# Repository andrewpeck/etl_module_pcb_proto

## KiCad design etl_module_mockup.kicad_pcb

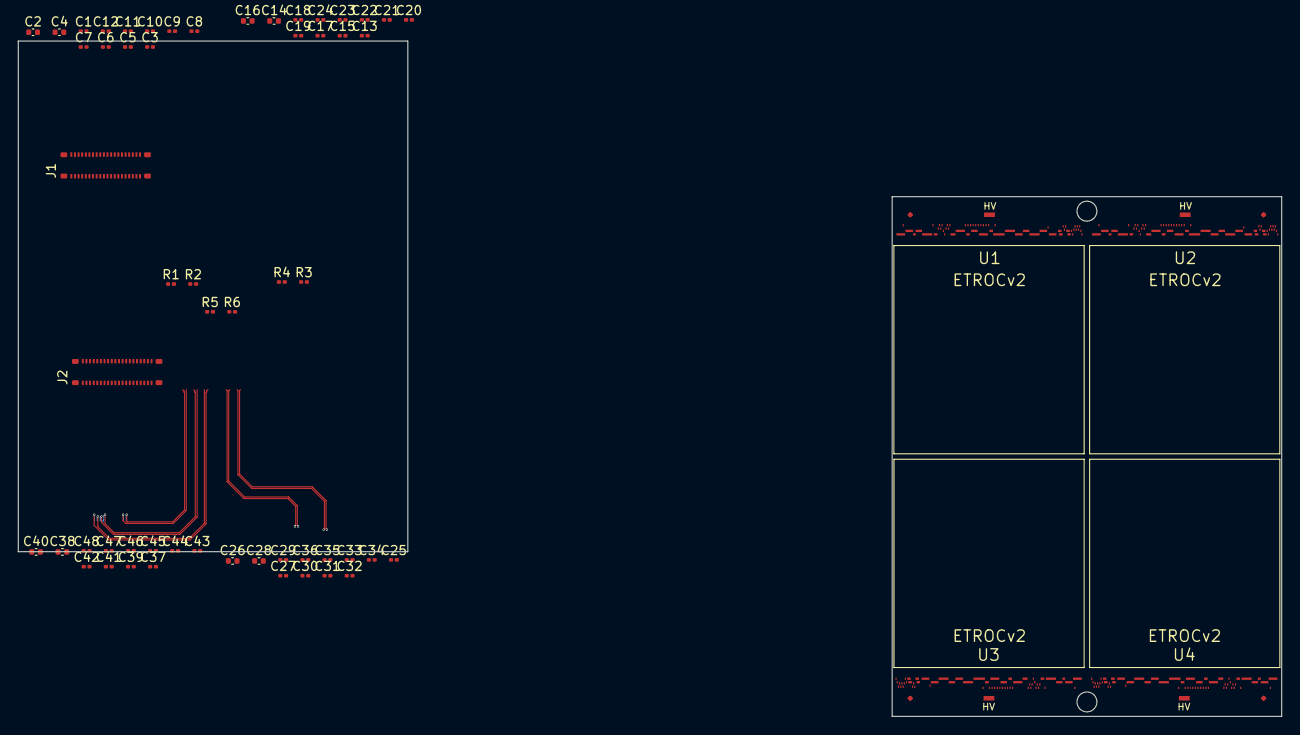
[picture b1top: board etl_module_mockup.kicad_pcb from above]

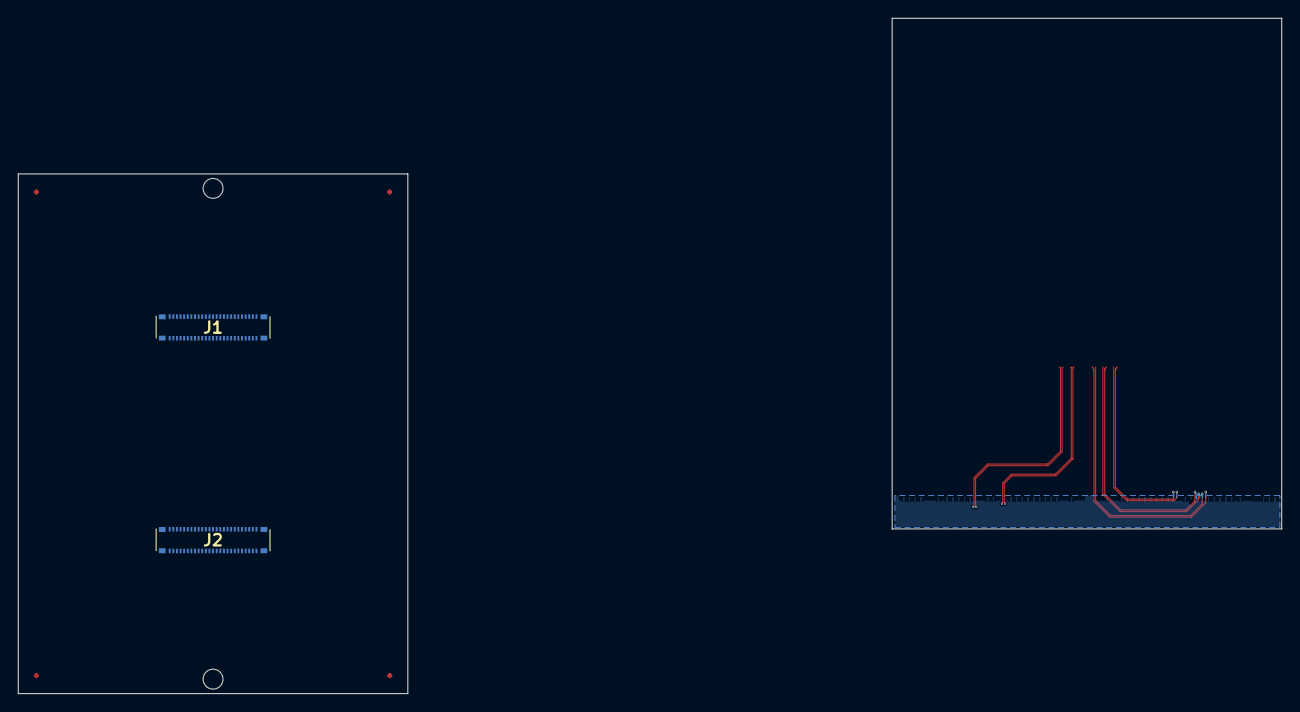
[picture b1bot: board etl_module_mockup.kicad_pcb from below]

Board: 2 copper layers, 62 parts (2 on the bottom side), 34 nets.

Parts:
C1, C3, C5, C6, C7, C8, C9, C10, C11, C12, C13, C15, C17, C18, C19, C20, C21, C22, C23, C24, C25, C27, C29, C30, C31, C32, C33, C34, C35, C36, C37, C39, C41, C42, C43, C44, C45, C46, C47, C48: 0.1uF; C_0201_0603Metric
C2, C4, C14, C16, C26, C28, C38, C40: 1uF; C_0402_1005Metric
J1, J2: WP7B-S040VA1
J1#2, J2#2: WP7B-S050VA1-R8000; WP7BS050VA1R8000
R1: 0R; R_0201_0603Metric
R2, R3, R4: 10k; R_0201_0603Metric
R5, R6: 1.2k 0.5%; R_0201_0603Metric
U1, U2, U3, U4: ETROCv2; PCB_ETROC2_test

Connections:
/1V0A: J1.20, R1.2
/1V2A: C38.1, C39.1, C40.1, C41.1, C42.1, C43.1, C44.1, C45.1, C46.1, C47.1, C48.1, J1.1, J1.2, J1.3, J1.4, J1.5, R2.1, R3.1, R4.1, R6.1, U4.1, U4.3, U4.5, U4.7, U4.13, U4.16, U4.18, U4.20, U4.22, U4.24, U4.30, U4.32, U4.38, U4.40, U4.42
/1V2B: C14.1, C15.1, C16.1, C17.1, C18.1, C19.1, C20.1, C21.1, C22.1, C23.1, C24.1, J1.6, J1.7, J1.8, J1.9, J1.10, U2.1, U2.3, U2.5, U2.7, U2.9, U2.13, U2.16, U2.18, U2.20, U2.22, U2.24, U2.30, U2.32, U2.38, U2.40, U2.42
/1V2C: C26.1, C27.1, C28.1, C29.1, C30.1, C31.1, C32.1, C33.1, C34.1, C35.1, C36.1, J2.1, J2.2, J2.3, J2.4, J2.5, R5.1, U3.1, U3.3, U3.5, U3.7, U3.10, U3.13, U3.16, U3.18, U3.20, U3.22, U3.24, U3.30, U3.32, U3.38, U3.40, U3.42
/1V2D: C2.1, C3.1, C4.1, C5.1, C6.1, C7.1, C8.1, C9.1, C10.1, C11.1, C12.1, J2.6, J2.7, J2.8, J2.9, J2.10, U1.1, U1.3, U1.5, U1.7, U1.9, U1.10, U1.13, U1.16, U1.18, U1.20, U1.22, U1.24, U1.30, U1.32, U1.38, U1.40, U1.42
/1V2_MON0: J1.17, R6.2
/1V2_MON1: J1.18, R5.2
/ADDR2: J2.11, U1.11, U2.11, U3.11, U4.11
/ADDR3: J2.12, U1.12, U2.12, U3.12, U4.12
/CLK0_N: J1.40, U4.37
/CLK0_P: J1.39, U4.36
/CLK1_N: J1.28, U2.37
/CLK1_P: J1.27, U2.36
/CLK2_N: J2.40, U3.37
/CLK2_P: J2.39, U3.36
/CLK3_N: J2.28, U1.37
/CLK3_P: J2.27, U1.36
/DIN0_N: J1.34, U4.27
/DIN0_P: J1.33, U4.26
/DIN1_N: J1.25, U2.27
/DIN1_P: J1.24, U2.26
/DIN2_N: J2.34, U3.27
/DIN2_P: J2.33, U3.26
/DIN3_N: J2.25, U1.27
/DIN3_P: J2.24, U1.26
/DOUT0_N: J1.37, U2.29, U4.29
/DOUT0_P: J1.36, U2.28, U4.28
/DOUT1_N: J2.37, U1.29, U3.29
/DOUT1_P: J2.36, U1.28, U3.28
/RSTN: J1.16, R4.2
/SCL: J2.20, R2.2
/SDA: J2.18, R3.2
/VREF: C1.1, C13.1, C25.1, C37.1, R1.1, U1.15, U2.15, U3.15, U4.15
GND: C1.2, C2.2, C3.2, C4.2, C5.2, C6.2, C7.2, C8.2, C9.2, C10.2, C11.2, C12.2, C13.2, C14.2, C15.2, C16.2, C17.2, C18.2, C19.2, C20.2, C21.2, C22.2, C23.2, C24.2, C25.2, C26.2, C27.2, C28.2, C29.2, C30.2, C31.2, C32.2, C33.2, C34.2, C35.2, C36.2, C37.2, C38.2, C39.2, C40.2, C41.2, C42.2, C43.2, C44.2, C45.2, C46.2, C47.2, C48.2, J1.11, J1.12, J1.13, J1.14, J1.15, J1.19, J1.23, J1.26, J1.29, J1.32, J1.35, J1.38, J1.41, J1.42, J1.43, J1.44, J2.13, J2.14, J2.15, J2.17, J2.19, J2.23, J2.26, J2.29, J2.32, J2.35, J2.38, J2.41, J2.42, J2.43, J2.44, U1.2, U1.4, U1.6, U1.8, U1.14, U1.17, U1.19, U1.23, U1.25, U1.31, U1.33, U1.39, U1.41, U1.43, U2.2, U2.4, U2.6, U2.8, U2.10, U2.14, U2.17, U2.19, U2.23, U2.25, U2.31, U2.33, U2.39, U2.41, U2.43, U3.2, U3.4, U3.6, U3.8, U3.9, U3.14, U3.17, U3.19, U3.23, U3.25, U3.31, U3.33, U3.39, U3.41, U3.43, U4.2, U4.4, U4.6, U4.8, U4.9, U4.10, U4.14, U4.17, U4.19, U4.23, U4.25, U4.31, U4.33, U4.39, U4.41, U4.43

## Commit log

2022-06-03 init
2022-06-03 remove converted files
2022-06-03 wip save
